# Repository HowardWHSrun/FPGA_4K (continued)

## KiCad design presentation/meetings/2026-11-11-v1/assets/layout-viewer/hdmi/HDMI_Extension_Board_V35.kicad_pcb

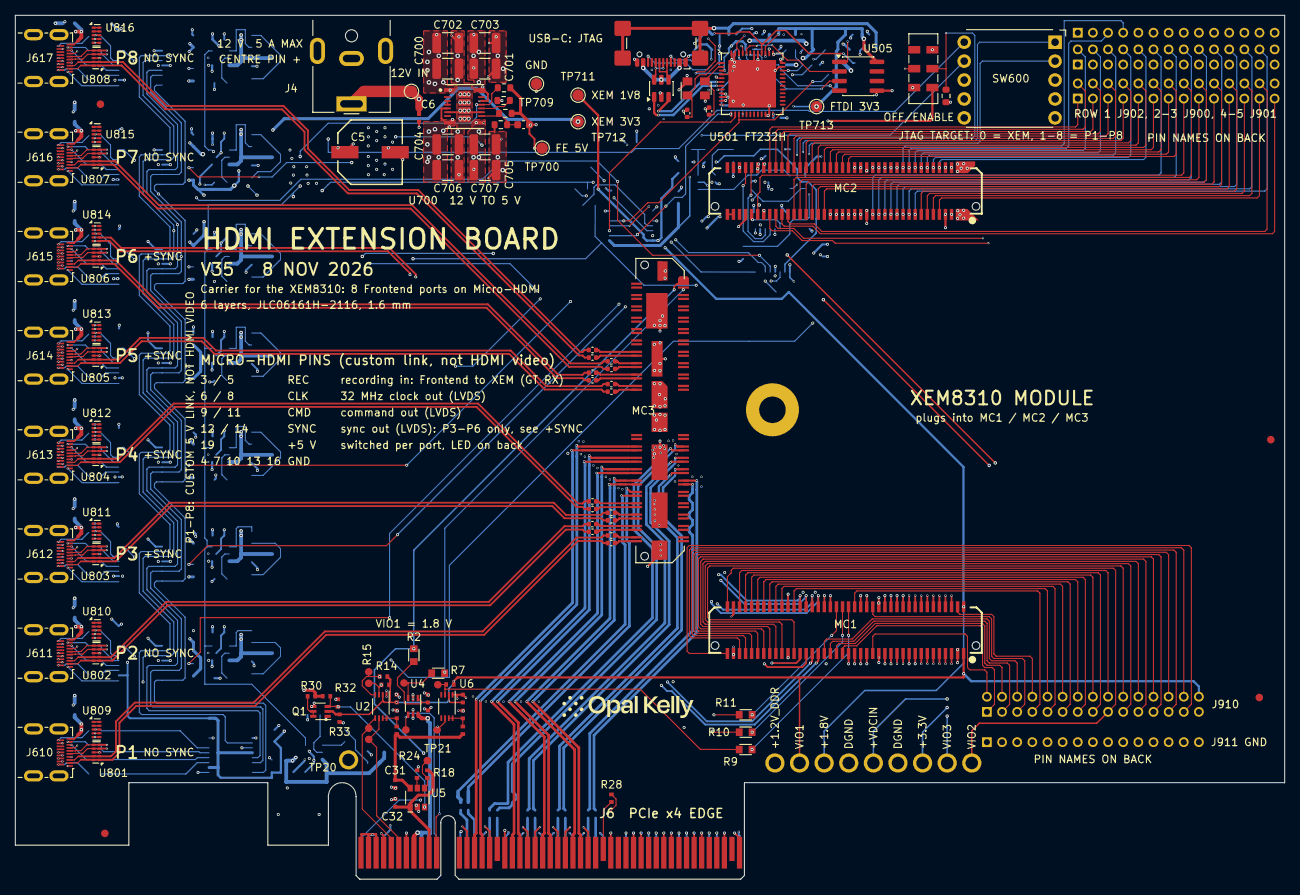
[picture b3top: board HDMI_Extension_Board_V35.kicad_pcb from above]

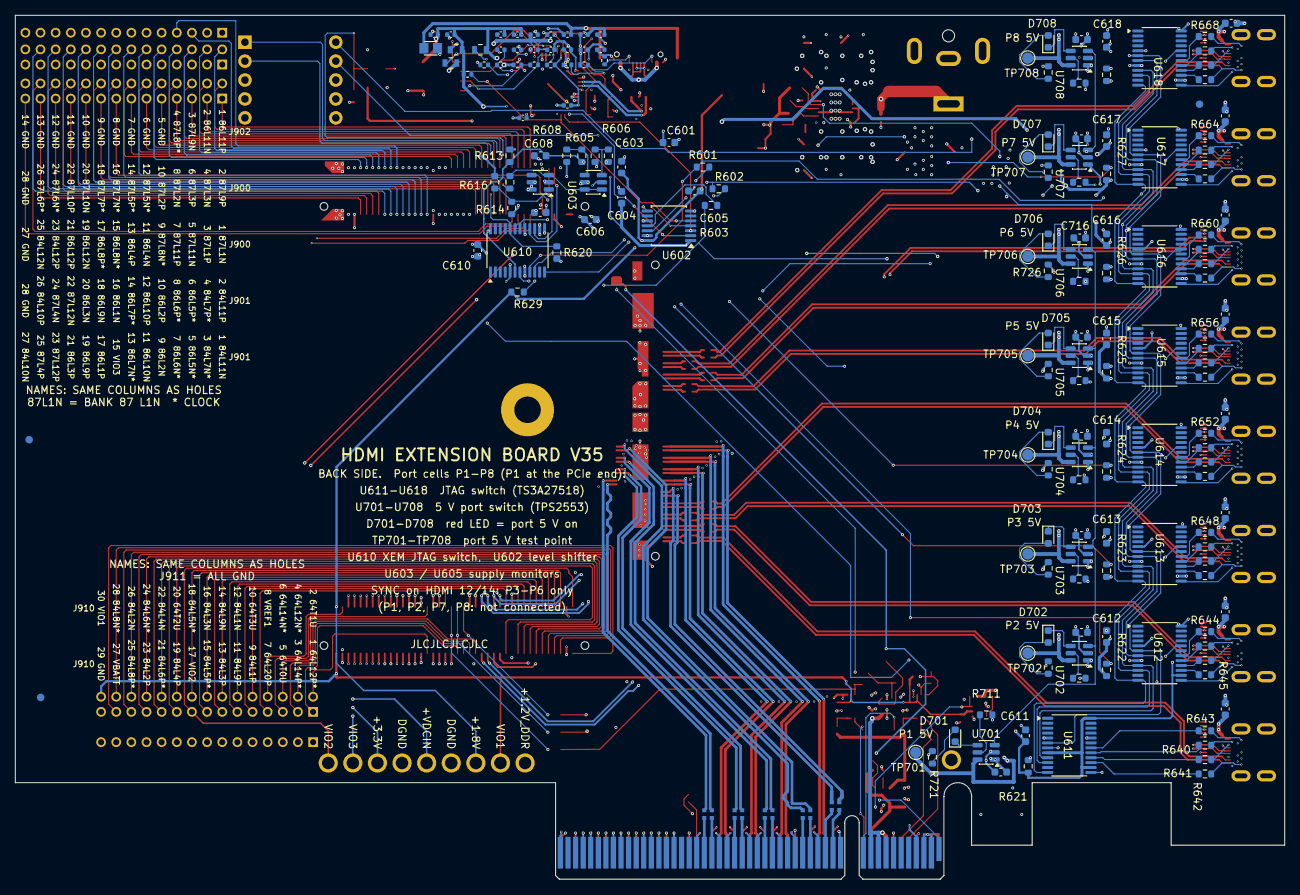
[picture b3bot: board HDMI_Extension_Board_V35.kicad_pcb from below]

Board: 6 copper layers, 167.6 x 114.1 mm, 309 parts (181 on the bottom side), 388 nets.

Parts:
*: Opal Kelly Logo; BRK_Logo_c689e08d
C5: EEE-FK1E221P; BRK_C5
C6: TMK105BJ104KV-F; BRK_C6
C7: C0402C104K8PACTU; BRK8310_C7
C8: C0402C104K8PACTU; BRK8310_C8
C9: C0402C104K8PACTU; BRK8310_C9
C10: C0402C104K8PACTU; BRK8310_C10
C11: C0402C104K8PACTU; BRK8310_C11
C12: C0402C104K8PACTU; BRK8310_C12
C13: CL05B224KO5NNNC; BRK8310_C13
C14: CL05B224KO5NNNC; BRK8310_C14
C15: CL05B224KO5NNNC; BRK8310_C15
C16: CL05B224KO5NNNC; BRK8310_C16
C17: CL05B224KO5NNNC; BRK8310_C17
C18: CL05B224KO5NNNC; BRK8310_C18
C19: CL05B224KO5NNNC; BRK8310_C19
C20: CL05B224KO5NNNC; BRK8310_C20
C27: C0402C104K8PACTU; BRK8310_C27
C28: C0402C104K8PACTU; BRK8310_C28
C31: C0402C104K8PACTU; BRK8310_C31
C32: C0402C104K8PACTU; BRK8310_C32
C500: 4.7u; C500
C501: 100n; C501
C502: 100n; C502
C503: 18p; C503
C504: 18p; C504
C505: 100n; C505
C506: 100n; C506
C507: 4.7u; C507
C508: 100n; C508
C509: 100n; C509
C510: 100n; C510
C511: 100n; C511
C512: 4.7u; C512
C513: 4.7u; C513
C514: 100n; C514
C515: 4.7u; C515
C516: 100n; C516
C517: 100n; C517
C518: 100n; C518
C519: 10n; C519
C601, C603: 2.2u; C_0603_1608Metric
C604, C605, C606, C609, C610, C611, C612, C613, C614, C615, C616, C617, C618: 100n; C_0603_1608Metric
C608: 1n; C_0603_1608Metric
C700, C701, C702, C703: 10uF; C_1210_3225Metric
C704, C705, C706, C707: 47uF; C_1210_3225Metric
C708: 22pF; C_0603_1608Metric
C711, C712, C713, C714, C715, C716, C717, C718: 100nF; C_0603_1608Metric
C721, C722, C723, C724, C725, C726, C727, C728: 1uF; C_0603_1608Metric
C745, C746, C747, C748, C749, C750, C751, C752, C753, C754, C755, C756, C757, C758, C759, C760: CL05B104KO5NNNC; C_0402_1005Metric
D500: USBLC6-2SC6; D500
D701, D702, D703, D704, D705, D706, D707, D708: RED; LED_0603_1608Metric
FB500: 600R; FB500
FB501: 600R; FB501
FB502: 600R; FB502
FB503: 220R @100MHz; FB503
FID1, FID5, FID6, FID7: FIDUCIAL; BRK_FID1
FID2: FIDUCIAL; BRK_FID2
FID3: FIDUCIAL; BRK_FID3
FID4: FIDUCIAL; BRK_FID4
J4: PJ-063AH; BarrelJack_CUI_PJ-063AH_Horizontal
J6: PCIe x8 Card-Edge Connector; BRK8310_J6
J500: USB4110-GF-A; J500
J610, J611, J612, J613, J614, J615, J616, J617: 467651001; HDMI_Micro-D_Molex_46765-1xxx
J900, J901: Conn_02x14_Odd_Even; HDR_Holes_2x14_P2.00mm
J902: Conn_01x14; HDR_Holes_1x14_P2.00mm
J910: Conn_02x15_Odd_Even; HDR_Holes_2x15_P2.00mm
J911: Conn_01x15; HDR_Holes_1x15_P2.00mm
J920: Voltage test holes; VHoles_1x09_P3.25mm_D1.651
MC1: BTE-040-01-F-D-A; BRK_MC1
MC2: BTE-040-01-F-D-A; BRK_MC2
MC3: QTH-040-01-F-D-DP-A; BRK_MC3
Q1: SI1922EDH-T1-GE3; BRK8310_Q1
R2: CRCW06030000Z0EA; BRK8310_R2
R7: CRCW06030000Z0EA; BRK8310_R7
R9: CRCW06030000Z0EA; BRK8310_R9
R10: CRCW06030000Z0EA; BRK8310_R10
R11: CRCW06030000Z0EA; BRK8310_R11
R13: CRCW0402200KFKED; BRK8310_R13
R14: CRCW04024K75FKED; BRK8310_R14
R15: CRCW04024K75FKED; BRK8310_R15
R18: CRCW0402100KFKED; BRK8310_R18
R23: CRCW0402200KFKED; BRK8310_R23
R24: CRCW0402100KFKED; BRK8310_R24
R25: CRCW0402100KFKED; BRK8310_R25
R28: CRCW04020000Z0ED; BRK8310_R28
R30: CRCW04024K75FKED; BRK8310_R30
R31: CRCW04024K75FKED; BRK8310_R31
R32: CRCW0402100KFKED; BRK8310_R32
R33: CRCW0402100KFKED; BRK8310_R33
R500: 5.1k 1%; R500
R501: 5.1k 1%; R501
R502: 100k; R502
R503: 100k; R503
R504: 2k; R504
R505: 10k; R505
R506: 10k; R506
R507: 12k 1%; R507
R509: 10k; R509
R600, R721, R722, R723, R724, R725, R726, R727, R728: 3.3k; R_0603_1608Metric
R601, R602, R603: 22R; R_0603_1608Metric
R605: 301k; R_0603_1608Metric
R606, R608, R616: 100k; R_0603_1608Metric
R607: 402k; R_0603_1608Metric
R613: 68k; R_0603_1608Metric
R614: 4.7k; R_0603_1608Metric
R615: 12k; R_0603_1608Metric
R620, R621, R622, R623, R624, R625, R626, R627, R628, R701, R703: 10k; R_0603_1608Metric
R629: 1k; R_0603_1608Metric
R640, R641, R642, R643, R644, R645, R646, R647, R648, R649, R650, R651, R652, R653, R654, R655, R656, R657, R658, R659, R660, R661, R662, R663, R664, R665, R666, R667, R668, R669, R670, R671: 100R; R_0603_1608Metric
R700: 40.2k; R_0603_1608Metric
R702: 13k; R_0603_1608Metric
R711, R712, R713, R714, R715, R716, R717, R718: 37.4k; R_0603_1608Metric
SW600: SRBQ490100; ALPS_SRBQ490100_1P9T
SW601: JS202011JCQN; SW700
TP9: SMDAT_VIO; BRK8310_TP9
TP10: SMDAT_PCIE; BRK8310_TP10
TP11: SMCLK_PCIE; BRK8310_TP11
TP12: SMCLK_VIO; BRK8310_TP12
TP13: PERST_VIO; BRK8310_TP13
TP14: PERST_PCIE; BRK8310_TP14
TP15: WAKE_VIO; BRK8310_TP15
TP16: WAKE_PCIE; BRK8310_TP16
TP20: +12V_PCIE_C; BRK8310_TP20
TP21: FAULT; BRK8310_TP21
TP700, TP701, TP702, TP703, TP704, TP705, TP706, TP707, TP708, TP709: TestPoint; TestPoint_Pad_D1.5mm
TP710: 12V_IN; TestPoint_Pad_D1.5mm
TP711: 1V8_XEM; TestPoint_Pad_D1.5mm
TP712: 3V3_XEM; TestPoint_Pad_D1.5mm
TP713: 3V3_FTDI; TestPoint_Pad_D1.5mm
U2: PCA9306DCUR; BRK8310_U2
U4: SN74AXC1T45DCK; BRK8310_U4
U5: AP22653AW6-7; BRK8310_U5
U6: PCA9306DCUR; BRK8310_U6
U501: FT232HQ-REEL; U501
U505: 93LC56BT-I/SN; SOIC-8_3.9x4.9mm_P1.27mm
U602: TXU0304PWR; TSSOP-14_4.4x5mm_P0.65mm
U603: TPS3700DDCR; SOT-23-6
U605: TPS3808G30DBVR; SOT-23-6
U610, U611, U612, U613, U614, U615, U616, U617, U618: TS3A27518EPWR; TSSOP-24_4.4x7.8mm_P0.65mm
U700: TPSM63606RDLR; TI_TPSM63606_RDL0020A_EVM
U701, U702, U703, U704, U705, U706, U707, U708: TPS2553DBVR; SOT-23-6
U801, U802, U803, U804, U805, U806, U807, U808, U809, U810, U811, U812, U813, U814, U815, U816: TPD4E02B04DQAR; USON-10_2.5x1.0mm_P0.5mm
Y500: 7U12000E18UCG 12MHz; Y500

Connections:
+1.2V_DDR: J920.1, MC3.80, R2.2
+1.8V: C603.1, C605.1, J920.3, MC1.2, R629.2, TP711.1, U602.14
+3.3V: C601.1, C606.1, C609.1, C610.1, C611.1, C612.1, C613.1, C614.1, C615.1, C616.1, C617.1, C618.1, J920.7, MC2.70, R30.2, R31.2, R615.1, R620.1, R621.1, R622.1, R623.1, R624.1, R625.1, R626.1, R627.1, R628.1, SW601.5, TP712.1, U603.5, U605.5, U605.6, U610.8, U610.14, U610.24, U611.8, U611.14, U611.24, U612.8, U612.14, U612.24, U613.8, U613.14, U613.24, U614.8, U614.14, U614.24, U615.8, U615.14, U615.24, U616.8, U616.14, U616.24, U617.8, U617.14, U617.24, U618.8, U618.14, U618.24
+3.3VAUX_PCIE: C31.2, R13.2, R23.2, U5.6
+3.3VAUX_PCIE_C: C32.2, J6.B10, R18.2, U5.1
+3.3V_PCIE_C: C12.2, J6.A9, J6.A10, J6.B8, U4.6
+VDCIN: C5.1, C6.2, C700.1, C701.1, C702.1, C703.1, J4.1, J920.5, MC2.1, MC2.2, MC2.3, MC2.4, TP710.1, U700.1, U700.14, U700.16
/+12V_PCIE_C: J6.A2, J6.A3, J6.B1, J6.B2, J6.B3, TP20.1
/FTDI3V3_PHY: C515.1, C516.1, FB501.2, U501.3
/FTDI3V3_PLL: C513.1, C514.1, FB500.2, U501.8
/FTDI5V_FILTERED: C500.1, C501.1, FB502.2, U501.40
/FTDI_EECLK: R503.2, U501.44, U505.2
/FTDI_EECS: R502.1, U501.45, U505.1
/FTDI_EEDATA: R504.1, U501.43, U505.3
/PCIE_PERST_B_3V3: J6.A11, TP14.1, U4.4
/PCIE_PERST_B_VIO: R7.1, TP13.1, U4.3
/PCIE_PRSNT1_B: J6.A1, R28.2
/PCIE_REFCLKN_C: C8.1, J6.A14
/PCIE_REFCLKP_C: C7.1, J6.A13
/PCIE_RX0N_C: C14.1, J6.A17
/PCIE_RX0P_C: C13.1, J6.A16
/PCIE_RX1N_C: C16.1, J6.A22
/PCIE_RX1P_C: C15.1, J6.A21
/PCIE_RX2N_C: C18.1, J6.A26
/PCIE_RX2P_C: C17.1, J6.A25
/PCIE_RX3N_C: C20.1, J6.A30
/PCIE_RX3P_C: C19.1, J6.A29
/PCIE_SMCLK_3V3: J6.B5, TP11.1, U2.5
/PCIE_SMCLK_VIO: R11.1, R14.1, TP12.1, U2.4
/PCIE_SMDAT_3V3: J6.B6, TP10.1, U2.6
/PCIE_SMDAT_VIO: R10.1, R15.1, TP9.1, U2.3
/PCIE_WAKE_B_3V3: J6.B11, TP16.1, U6.6
/PCIE_WAKE_B_VIO: R9.1, R25.1, TP15.1, U6.3
/VIO_PG: Q1.3, R31.1, R32.2, U5.3
B64_L1N: J614.8, MC1.12, U813.4, U813.7
B64_L1P: J614.6, MC1.10, U813.5, U813.6
B64_L2N: J615.11, MC1.16, U806.5, U806.6
B64_L2P: J615.9, MC1.14, U806.4, U806.7
B64_L3N: J611.11, MC1.15, U802.5, U802.6
B64_L3P: J611.9, MC1.13, U802.4, U802.7
B64_L4N: J614.11, MC1.8, U805.5, U805.6
B64_L4P: J614.9, MC1.6, U805.4, U805.7
B64_L5N: J610.11, MC1.7, U801.5, U801.6
B64_L5P: J610.9, MC1.5, U801.4, U801.7
B64_L6N: J610.8, MC1.11, U809.4, U809.7
B64_L6P: J610.6, MC1.9, U809.5, U809.6
B64_L7N: J612.11, MC1.23, U803.5, U803.6
B64_L7P: J612.9, MC1.21, U803.4, U803.7
B64_L8N: J615.8, MC1.20, U814.4, U814.7
B64_L8P: J615.6, MC1.18, U814.5, U814.6
B64_L9N: J616.11, MC1.24, U807.5, U807.6
B64_L9P: J616.9, MC1.22, U807.4, U807.7
B64_L10N: J616.8, MC1.28, U815.4, U815.7
B64_L10P: J616.6, MC1.26, U815.5, U815.6
B64_L11N_GC: J613.8, MC1.39, U812.4, U812.7
B64_L11P_GC: J613.6, MC1.37, U812.5, U812.6
B64_L12N_GC: J910.4, MC1.43
B64_L12P_GC: J910.1, MC1.41
B64_L13N_GC: J612.8, MC1.27, U811.4, U811.7
B64_L13P_GC: J612.6, MC1.25, U811.5, U811.6
B64_L14N_GC: J910.6, MC1.47
B64_L14P_GC: J910.3, MC1.45
B64_L15N: J613.11, MC1.35, U804.5, U804.6
B64_L15P: J613.9, MC1.33, U804.4, U804.7
B64_L16N: J612.14, MC1.51, U811.1, U811.10
B64_L16P: J612.12, MC1.49, U811.2, U811.9
B64_L17N: MC1.44, R11.2
B64_L17P: MC1.42, R10.2
B64_L18N: J615.14, MC1.56, U814.1, U814.10
B64_L18P: J615.12, MC1.54, U814.2, U814.9
B64_L19N: J611.8, MC1.19, U810.4, U810.7
B64_L19P: J611.6, MC1.17, U810.5, U810.6
B64_L20N: MC1.40, R9.2
B64_L20P: J910.7, MC1.38
B64_L21N: J617.11, MC1.36, U808.5, U808.6
B64_L21P: J617.9, MC1.34, U808.4, U808.7
B64_L22N: J614.14, MC1.52, U813.1, U813.10
B64_L22P: J614.12, MC1.50, U813.2, U813.9
B64_L23N: J613.14, MC1.55, U812.1, U812.10
B64_L23P: J613.12, MC1.53, U812.2, U812.9
B64_L24N: J617.8, MC1.48, U816.4, U816.7
B64_L24P: J617.6, MC1.46, U816.5, U816.6
B64_T0U_N12: J910.5, MC1.32
B64_T1U_N12: J910.2, MC1.31
B64_T2U_N12: J910.20, MC1.57
B64_T3U_N12: J910.10, MC1.58
B67_T3U_N12: MC3.78, R7.2
B84_L1N: J910.12, MC1.64
B84_L1P: J910.9, MC1.62
B84_L2N: J910.26, MC1.71
B84_L2P: J910.23, MC1.69
B84_L3N: J910.16, MC1.72
B84_L3P: J910.13, MC1.70
B84_L4N: J910.22, MC1.63
B84_L4P: J910.19, MC1.61
B84_L5N_HDGC: J910.18, MC1.76
B84_L5P_HDGC: J910.15, MC1.74
B84_L6N_HDGC: J910.24, MC1.67
B84_L6P_HDGC: J910.21, MC1.65
B84_L7N_HDGC: J901.3, MC2.62
B84_L7P_HDGC: J901.4, MC2.60
B84_L8N_HDGC: J910.28, MC1.75
B84_L8P_HDGC: J910.25, MC1.73
B84_L9N: J910.14, MC1.68
B84_L9P: J910.11, MC1.66
B84_L10N: J901.27, MC2.61
B84_L10P: J901.26, MC2.59
B84_L11N: J901.1, MC2.66
B84_L11P: J901.2, MC2.64
B84_L12N: J900.25, MC2.65
B84_L12P: J900.23, MC2.63
B86_L1N: J901.16, MC2.57
B86_L1P: J901.17, MC2.55
B86_L2N: J901.9, MC2.50
B86_L2P: J901.10, MC2.48
B86_L3N: J901.20, MC2.49
B86_L3P: J901.21, MC2.47
B86_L4N: J900.11, MC2.45
B86_L4P: J900.13, MC2.43
B86_L5N_HDGC: J901.5, MC2.58
B86_L5P_HDGC: J901.6, MC2.56
B86_L6N_HDGC: J901.7, MC2.54
B86_L6P_HDGC: J901.8, MC2.52
B86_L7N_HDGC: J901.13, MC2.42
B86_L7P_HDGC: J901.14, MC2.40
B86_L8N_HDGC: J900.15, MC2.41
B86_L8P_HDGC: J900.17, MC2.39
B86_L9N: J901.18, MC2.53
B86_L9P: J901.19, MC2.51
B86_L10N: J901.11, MC2.46
B86_L10P: J901.12, MC2.44
B86_L11N: J902.2, MC2.38
B86_L11P: J902.1, MC2.36
B86_L12N: J900.19, MC2.37
B86_L12P: J900.21, MC2.35
B87_L1N: J900.1, MC2.32
B87_L1P: J900.3, MC2.30
B87_L2N: J900.8, MC2.12
B87_L2P: J900.10, MC2.10
B87_L3N: J900.4, MC2.16
B87_L3P: J900.6, MC2.14
B87_L4N: J901.24, MC2.11
B87_L4P: J901.25, MC2.9
B87_L5N_HDGC: J900.12, MC2.31
B87_L5P_HDGC: J900.14, MC2.29
B87_L6N_HDGC: J900.24, MC2.19
B87_L6P_HDGC: J900.26, MC2.17
B87_L7N_HDGC: J900.16, MC2.27
B87_L7P_HDGC: J900.18, MC2.25
B87_L8N_HDGC: J900.9, MC2.24
B87_L8P_HDGC: J902.4, MC2.22
B87_L9N: J902.3, MC2.20
B87_L9P: J900.2, MC2.18
B87_L10N: J900.20, MC2.23
B87_L10P: J900.22, MC2.21
B87_L11N: J900.5, MC2.28
B87_L11P: J900.7, MC2.26
B87_L12N: J901.22, MC2.15
B87_L12P: J901.23, MC2.13
DGND: C5.2, C6.1, C9.1, C10.1, C11.1, C12.1, C27.1, C28.1, C31.1, C32.1, C500.2, C501.2, C502.2, C503.2, C504.2, C505.2, C506.1, C507.2, C508.2, C509.2, C510.2, C511.2, C512.2, C513.2, C514.2, C515.2, C516.2, C517.1, C518.1, C519.2, C601.2, C603.2, C604.2, C605.2, C606.2, C608.2, C609.2, C610.2, C611.2, C612.2, C613.2, C614.2, C615.2, C616.2, C617.2, C618.2, C700.2, C701.2, C702.2, C703.2, C704.2, C705.2, C706.2, C707.2, C711.2, C712.2, C713.2, C714.2, C715.2, C716.2, C717.2, C718.2, C721.2, C722.2, C723.2, C724.2, C725.2, C726.2, C727.2, C728.2, D500.2, FB503.1, J4.2, J6.A4, J6.A12, J6.A15, J6.A18, J6.A20, J6.A23, J6.A24, J6.A27, J6.A28, J6.A31, J6.A34, J6.A37, J6.A38, J6.A41, J6.A42, J6.A45, J6.A46, J6.A49, J6.B4, J6.B7, J6.B13, J6.B16, J6.B18, J6.B21, J6.B22, J6.B25, J6.B26, J6.B29, J6.B32, J6.B35, J6.B36, J6.B39, J6.B40, J6.B43, J6.B44, J6.B47, J6.B49, J500.A1, J500.A12, J500.B1, J500.B12, J610.4, J610.7, J610.10, J610.13, J610.16, J610.SH, J611.4, J611.7, J611.10, J611.13, J611.16, J611.SH, J612.4, J612.7, J612.10, J612.13, J612.16, J612.SH, J613.4, J613.7, J613.10, J613.13, J613.16, J613.SH, J614.4, J614.7, J614.10, J614.13, J614.16, J614.SH, J615.4, J615.7, J615.10, J615.13, J615.16, J615.SH, J616.4, J616.7, J616.10, J616.13, J616.16, J616.SH, J617.4, J617.7, J617.10, J617.13, J617.16, J617.SH, J900.27, J900.28, J901.28, J902.5, J902.6, J902.7, J902.8, J902.9, J902.10, J902.11, J902.12, J902.13, J902.14, J910.29, J911.1, J911.2, J911.3, J911.4, J911.5, J911.6, J911.7, J911.8, J911.9, J911.10, J911.11, J911.12, J911.13, J911.14, J911.15, J920.4, J920.6, MC1.3, MC1.29, MC1.30, MC1.59, MC1.60, MC1.77, MC1.78, MC2.5, MC2.6, MC2.7, MC2.8, MC2.33, MC2.34, MC2.67, MC2.68, MC2.73, MC3.0, Q1.1, Q1.4, R24.1, R32.1, R33.1, R500.1, R501.2, R502.2, R507.2, R600.2, R606.1, R608.1, R613.2, R616.2, R701.1, R702.1, R711.1, R712.1, R713.1, R714.1, R715.1, R716.1, R717.1, R718.1, SW601.1, SW601.7, TP709.1, U2.1, U4.2, U4.5, U5.2, U6.1, U501.4, U501.9, U501.10, U501.11, U501.22, U501.23, U501.35, U501.36, U501.41, U501.42, U501.47, U501.48, U501.PAD, U505.5, U602.7, U603.2, U605.2, U610.5, U611.5, U612.5, U613.5, U614.5, U615.5, U616.5, U617.5, U618.5, U700.6, U700.11, U700.17, U700.18, U700.19, U700.20, U701.2, U702.2, U703.2, U704.2, U705.2, U706.2, U707.2, U708.2, U801.3, U801.8, U802.3, U802.8, U803.3, U803.8, U804.3, U804.8, U805.3, U805.8, U806.3, U806.8, U807.3, U807.8, U808.3, U808.8, U809.3, U809.8, U810.3, U810.8, U811.3, U811.8, U812.3, U812.8, U813.3, U813.8, U814.3, U814.8, U815.3, U815.8, U816.3, U816.8, Y500.2, Y500.4
DRIVE_ENABLE: R615.2, R616.1, U602.8, U605.1
FE_5V: C704.1, C705.1, C706.1, C707.1, C708.1, C711.1, C712.1, C713.1, C714.1, C715.1, C716.1, C717.1, C718.1, R700.2, R703.2, R721.2, R722.2, R723.2, R724.2, R725.2, R726.2, R727.2, R728.2, TP700.1, U700.5, U700.8, U700.9, U701.1, U702.1, U703.1, U704.1, U705.1, U706.1, U707.1, U708.1
FTDI3V3: C505.1, C507.1, C508.1, C509.1, C510.1, C511.1, C512.1, C604.1, FB500.1, FB501.1, R503.1, R505.2, R506.1, R509.2, TP713.1, U501.12, U501.24, U501.39, U501.46, U505.8, U602.1
GNDADC: MC2.77, MC2.79
HDMI1_JTAG_TCK: J610.17, R640.2
HDMI1_JTAG_TDI: J610.15, R641.2
HDMI1_JTAG_TDO: J610.18, R643.2
HDMI1_JTAG_TMS: J610.2, R642.2
HDMI1_VREF: J610.1, U611.13
HDMI2_JTAG_TCK: J611.17, R644.2
HDMI2_JTAG_TDI: J611.15, R645.2
HDMI2_JTAG_TDO: J611.18, R647.2
HDMI2_JTAG_TMS: J611.2, R646.2
HDMI2_VREF: J611.1, U612.13
HDMI3_JTAG_TCK: J612.17, R648.2
HDMI3_JTAG_TDI: J612.15, R649.2
HDMI3_JTAG_TDO: J612.18, R651.2
HDMI3_JTAG_TMS: J612.2, R650.2
HDMI3_VREF: J612.1, U613.13
HDMI4_JTAG_TCK: J613.17, R652.2
HDMI4_JTAG_TDI: J613.15, R653.2
HDMI4_JTAG_TDO: J613.18, R655.2
HDMI4_JTAG_TMS: J613.2, R654.2
HDMI4_VREF: J613.1, U614.13
HDMI5_JTAG_TCK: J614.17, R656.2
HDMI5_JTAG_TDI: J614.15, R657.2
HDMI5_JTAG_TDO: J614.18, R659.2
HDMI5_JTAG_TMS: J614.2, R658.2
HDMI5_VREF: J614.1, U615.13
HDMI6_JTAG_TCK: J615.17, R660.2
HDMI6_JTAG_TDI: J615.15, R661.2
HDMI6_JTAG_TDO: J615.18, R663.2
HDMI6_JTAG_TMS: J615.2, R662.2
HDMI6_VREF: J615.1, U616.13
HDMI7_JTAG_TCK: J616.17, R664.2
HDMI7_JTAG_TDI: J616.15, R665.2
HDMI7_JTAG_TDO: J616.18, R667.2
HDMI7_JTAG_TMS: J616.2, R666.2
HDMI7_VREF: J616.1, U617.13
HDMI8_JTAG_TCK: J617.17, R668.2
HDMI8_JTAG_TDI: J617.15, R669.2
HDMI8_JTAG_TDO: J617.18, R671.2
HDMI8_JTAG_TMS: J617.2, R670.2
HDMI8_VREF: J617.1, U618.13
HOST_TCK: U501.13, U602.2
HOST_TDI: U501.14, U602.3
HOST_TDO: R509.1, U501.15, U602.5
HOST_TMS: U501.16, U602.4
JTAG_TCK: MC2.76, U610.17
JTAG_TCK_1V8: R601.2, U610.9, U611.9, U612.9, U613.9, U614.9, U615.9, U616.9, U617.9, U618.9
JTAG_TDI: MC2.74, U610.16
JTAG_TDI_1V8: R602.2, U610.12, U611.12, U612.12, U613.12, U614.12, U615.12, U616.12, U617.12, U618.12
JTAG_TDO: MC2.71, U610.18
JTAG_TDO_1V8: U602.10, U610.10, U611.10, U612.10, U613.10, U614.10, U615.10, U616.10, U617.10, U618.10
JTAG_TMS: MC2.72, U610.15
JTAG_TMS_1V8: R603.2, U610.7, U611.7, U612.7, U613.7, U614.7, U615.7, U616.7, U617.7, U618.7
MASTER: R600.1, R614.1, SW601.6
MGT_REFCLK1N_225_C: C8.2, MC3.19
MGT_REFCLK1P_225_C: C7.2, MC3.17
MGT_RXN0_224: C746.1, J610.5, U801.2, U801.9
MGT_RXN0_225: J6.B28, MC3.23
MGT_RXN0_226: C754.1, J614.5, U805.2, U805.9
MGT_RXN1_224: C748.1, J611.5, U802.2, U802.9
MGT_RXN1_225: J6.B24, MC3.27
MGT_RXN1_226: C756.1, J615.5, U806.2, U806.9
MGT_RXN2_224: C750.1, J612.5, U803.2, U803.9
MGT_RXN2_225: J6.B20, MC3.31
MGT_RXN2_226: C758.1, J616.5, U807.2, U807.9
MGT_RXN3_224: C752.1, J613.5, U804.2, U804.9
MGT_RXN3_225: J6.B15, MC3.35
MGT_RXN3_226: C760.1, J617.5, U808.2, U808.9
MGT_RXP0_224: C745.1, J610.3, U801.1, U801.10
MGT_RXP0_225: J6.B27, MC3.21
MGT_RXP0_226: C753.1, J614.3, U805.1, U805.10
MGT_RXP1_224: C747.1, J611.3, U802.1, U802.10
MGT_RXP1_225: J6.B23, MC3.25
MGT_RXP1_226: C755.1, J615.3, U806.1, U806.10
MGT_RXP2_224: C749.1, J612.3, U803.1, U803.10
MGT_RXP2_225: J6.B19, MC3.29
MGT_RXP2_226: C757.1, J616.3, U807.1, U807.10
MGT_RXP3_224: C751.1, J613.3, U804.1, U804.10
MGT_RXP3_225: J6.B14, MC3.33
MGT_RXP3_226: C759.1, J617.3, U808.1, U808.10
MGT_TXN0_225: C20.2, MC3.24
MGT_TXN1_225: C18.2, MC3.28
MGT_TXN2_225: C16.2, MC3.32
MGT_TXN3_225: C14.2, MC3.36
MGT_TXP0_225: C19.2, MC3.22
MGT_TXP1_225: C17.2, MC3.26
MGT_TXP2_225: C15.2, MC3.30
MGT_TXP3_225: C13.2, MC3.34
unnamed: C502.1, FB503.2, J500.M1, J500.M2, J500.M3, J500.M4
unnamed: D701.2, R721.1
unnamed: D701.1, U701.4
unnamed: D702.2, R722.1
unnamed: D702.1, U702.4
unnamed: D703.2, R723.1
unnamed: D703.1, U703.4
unnamed: D704.2, R724.1
unnamed: D704.1, U704.4
unnamed: D705.2, R725.1
unnamed: D705.1, U705.4
unnamed: D706.2, R726.1
unnamed: D706.1, U706.4
unnamed: D707.2, R727.1
unnamed: D707.1, U707.4
unnamed: D708.2, R728.1
unnamed: D708.1, U708.4
unnamed: J6.B31, R28.1
unnamed: J500.A5, R500.2
unnamed: J500.B5, R501.1
unnamed: C746.2, MC3.3
unnamed: C754.2, MC3.43
unnamed: C748.2, MC3.7
unnamed: C756.2, MC3.47
unnamed: C750.2, MC3.11
unnamed: C758.2, MC3.51
unnamed: C752.2, MC3.15
unnamed: C760.2, MC3.55
unnamed: C745.2, MC3.1
unnamed: C753.2, MC3.41
unnamed: C747.2, MC3.5
unnamed: C755.2, MC3.45
unnamed: C749.2, MC3.9
unnamed: C757.2, MC3.49
unnamed: C751.2, MC3.13
unnamed: C759.2, MC3.53
unnamed: Q1.5, Q1.6, R30.1
unnamed: R18.1, TP21.1, U5.4
unnamed: C10.2, R13.1, U2.7, U2.8
unnamed: C11.2, R2.1, U4.1
unnamed: R24.2, U5.5
unnamed: C28.2, R23.1, U6.7, U6.8
unnamed: C503.1, U501.1, Y500.1
unnamed: C504.1, U501.2, Y500.3
unnamed: R507.1, U501.5
unnamed: C518.2, U501.37
unnamed: C517.2, U501.38
unnamed: C519.1, R506.2, U501.34
unnamed: R504.2, R505.1, U505.4
unnamed: R601.1, U602.13
unnamed: R602.1, U602.12
unnamed: R603.1, U602.11
unnamed: R605.2, R606.2, U603.3
unnamed: R607.2, R608.2, U603.4
unnamed: R629.1, U610.13
unnamed: R642.1, U611.15
unnamed: R640.1, U611.17
unnamed: R643.1, U611.18
unnamed: R641.1, U611.16
unnamed: R646.1, U612.15
unnamed: R644.1, U612.17
unnamed: R647.1, U612.18
unnamed: R645.1, U612.16
unnamed: R650.1, U613.15
unnamed: R648.1, U613.17
unnamed: R651.1, U613.18
unnamed: R649.1, U613.16
unnamed: R654.1, U614.15
unnamed: R652.1, U614.17
unnamed: R655.1, U614.18
unnamed: R653.1, U614.16
unnamed: R658.1, U615.15
unnamed: R656.1, U615.17
unnamed: R659.1, U615.18
unnamed: R657.1, U615.16
unnamed: R662.1, U616.15
unnamed: R660.1, U616.17
unnamed: R663.1, U616.18
unnamed: R661.1, U616.16
unnamed: R666.1, U617.15
unnamed: R664.1, U617.17
unnamed: R667.1, U617.18
unnamed: R665.1, U617.16
unnamed: R670.1, U618.15
unnamed: R668.1, U618.17
unnamed: R671.1, U618.18
unnamed: R669.1, U618.16
unnamed: U700.3, U700.4
unnamed: C708.2, R700.1, R701.2, U700.10
unnamed: R702.2, U700.12
unnamed: R711.2, U701.5
unnamed: R712.2, U702.5
unnamed: R713.2, U703.5
unnamed: R714.2, U704.5
unnamed: R715.2, U705.5
unnamed: R716.2, U706.5
unnamed: R717.2, U707.5
unnamed: R718.2, U708.5
unnamed: U809.1, U809.10
unnamed: U809.2, U809.9
unnamed: U810.1, U810.10
unnamed: U810.2, U810.9
unnamed: U815.1, U815.10
unnamed: U815.2, U815.9
unnamed: U816.1, U816.10
unnamed: U816.2, U816.9
PORT1_5V: C721.1, J610.19, TP701.1, U701.6
PORT2_5V: C722.1, J611.19, TP702.1, U702.6
PORT3_5V: C723.1, J612.19, TP703.1, U703.6
PORT4_5V: C724.1, J613.19, TP704.1, U704.6
PORT5_5V: C725.1, J614.19, TP705.1, U705.6
PORT6_5V: C726.1, J615.19, TP706.1, U706.6
PORT7_5V: C727.1, J616.19, TP707.1, U707.6
PORT8_5V: C728.1, J617.19, TP708.1, U708.6
PORT_ENABLE: R703.1, U700.13, U701.3, U702.3, U703.3, U704.3, U705.3, U706.3, U707.3, U708.3
ROTARY_COMMON: SW600.3, SW601.2
SEL_0: R620.2, SW600.1, U610.20
SEL_1: R621.2, SW600.2, U611.20
SEL_2: R622.2, SW600.4, U612.20
SEL_3: R623.2, SW600.5, U613.20
SEL_4: R624.2, SW600.6, U614.20
SEL_5: R625.2, SW600.7, U615.20
SEL_6: R626.2, SW600.8, U616.20
SEL_7: R627.2, SW600.9, U617.20
SEL_8: R628.2, SW600.10, U618.20
USB5V: C506.2, D500.5, FB502.1, J500.A4, J500.A9, J500.B4, J500.B9
USB_DM_CONN: D500.4, J500.A7, J500.B7
USB_DP_CONN: D500.6, J500.A6, J500.B6
USB_D_N: D500.3, U501.6
USB_D_P: D500.1, U501.7
VBATT: J910.27, MC1.79
VIO1: C9.2, C27.2, J910.30, J920.2, MC1.1, Q1.2, R14.2, R15.2, R25.2, R33.2, U2.2, U6.2
VIO2: J910.17, J920.9, MC1.80
VIO3: J901.15, J920.8, MC2.69
VREF1: J910.8, MC1.4
VREF_SELECTED: C608.1, R605.1, R607.1, R613.1, U610.6, U611.6, U612.6, U613.6, U614.6, U615.6, U616.6, U617.6, U618.6
WINDOW_GATE: R614.2, U603.1, U603.6, U605.3

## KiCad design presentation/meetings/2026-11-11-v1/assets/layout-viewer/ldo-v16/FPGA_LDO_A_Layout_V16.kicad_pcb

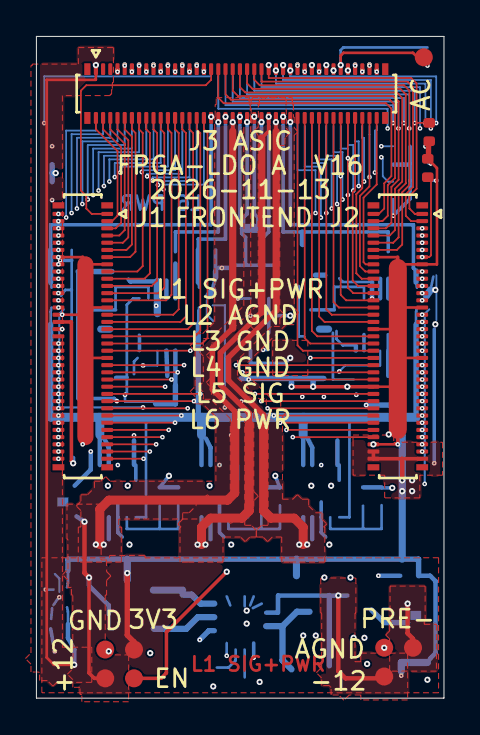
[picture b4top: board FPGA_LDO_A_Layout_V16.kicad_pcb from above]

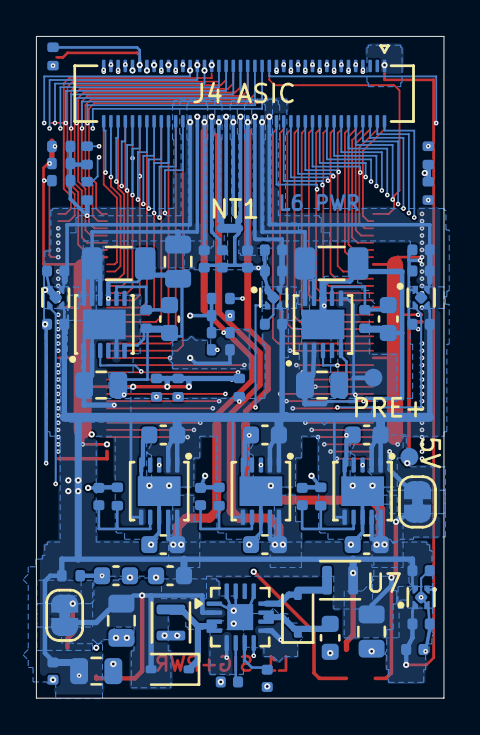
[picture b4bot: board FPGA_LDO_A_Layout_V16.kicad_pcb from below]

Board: 6 copper layers, 22.6 x 36.8 mm, 93 parts (80 on the bottom side), 149 nets.

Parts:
C1, C14, C21: 22uF; C_0805_2012Metric
C2: 100nF; C_0402_1005Metric
C3, C11: 4.7uF; C_0603_1608Metric
C15, C903, C1003: 1uF; C_0603_1608Metric
C16, C17: 10nF; C_0402_1005Metric
C51, C53, C54, C55, C56, C57, C203, C301, C302, C401, C402, C501, C502, C603, C701, C702, C803: 1uF; C_0402_1005Metric
C201, C202, C601, C602, C801, C802: 10uF; C_0603_1608Metric
C901, C1001, C1004: 10uF; C_0805_2012Metric
C902, C1002: 22uF; C_1206_3216Metric
D11, D12: B0540WS-TP; D_SOD-323
J1, J2: DF40C-70DP-0.4V(51); Hirose_DF40C-70DP-0.4V_2x35-1MP_P0.4mm
J3: DF40C-80DP-0.4V(51); Hirose_DF40C-80DP-0.4V_2x40-1MP_P0.4mm
J4: DF40C-80DS-0.4V(51); Hirose_DF40C-80DS-0.4V_2x40_P0.4mm
JP1, JP2: Bridged; SolderJumper-2_P1.3mm_Bridged_RoundedPad1.0x1.5mm
L11, L12: 6.8uH; L_Murata_DFE201610P
NT1: NetTie_2; NetTie-2_SMD_Pad0.5mm
R1, R2, R3, R4, R5, R6, R16, R17, R18, R19, R20, R21, R22, R23, R24, R25, R26, R27: 10k; R_0402_1005Metric
R201, R601: 15k; R_0402_1005Metric
R801: 7.5k; R_0402_1005Metric
R901, R1001: 80.6k; R_0402_1005Metric
TP1: VIN_3V3; TestPoint_Pad_D1.0mm_Compact
TP2: STIM_POS_12V; TestPoint_Pad_D1.0mm_Compact
TP3: STIM_NEG_12V; TestPoint_Pad_D1.0mm_Compact
TP4: EN_ASIC_RAILS; TestPoint_Pad_D1.0mm_Compact
TP5: GND; TestPoint_Pad_D1.0mm_Compact
TP6: AGND; TestPoint_Pad_D1.0mm_Compact
TP7: ASIC_AC_IN; TestPoint_Pad_D1.0mm_Compact
TP8: STIM_PRE_POS; TestPoint_Pad_D1.0mm_Compact
TP9: STIM_PRE_NEG; TestPoint_Pad_D1.0mm_Compact
TP10: VIN_5V; TestPoint_Pad_D1.0mm_Compact
U1: LT3582EUD-12#PBF; QFN-16-1EP_3x3mm_P0.5mm_EP1.45x1.45mm
U2, U6, U8, U9: LT3042EDD#PBF; DFN-10-1EP_3x3mm_P0.5mm_EP1.65x2.38mm
U3, U4, U5, U7: TPS7A2015PDQNR; Texas_X2SON-4_1x1mm_P0.65mm
U10: LT3094EDD#PBF; DFN-12-1EP_3x3mm_P0.45mm_EP1.65x2.38mm

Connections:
/ASIC1_CLK32MHz_Out: J2.59, J4.45
/ASIC1_DATA1: J2.21, J4.79
/ASIC1_DATA2: J2.64, J4.77
/ASIC1_DATA3: J2.62, J4.75
/ASIC1_DATA4: J2.60, J4.73
/ASIC1_DATA5: J2.57, J4.43
/ASIC1_DATA6: J2.55, J4.41
/ASIC1_DATA7: J2.53, J4.39
/ASIC1_DATA8: J2.51, J4.37
/ASIC1_READ: J2.49, J4.35
/ASIC1_SYNC: J2.61, J4.47
/ASIC2_CLK32MHz_Out: J1.63, J4.19
/ASIC2_DATA1: J1.70, J4.33
/ASIC2_DATA2: J1.51, J4.31
/ASIC2_DATA3: J1.53, J4.29
/ASIC2_DATA4: J1.55, J4.27
/ASIC2_DATA5: J1.65, J4.17
/ASIC2_DATA6: J1.67, J4.15
/ASIC2_DATA7: J1.69, J4.13
/ASIC2_DATA8: J1.38, J4.11
/ASIC2_READ: J1.40, J4.9
/ASIC2_SYNC: J1.61, J4.21
/ASIC3_4_TOP_SPI_CLK: J2.37, J4.72, R24.1
/ASIC3_4_TOP_SPI_LATCH: J2.35, J4.70, R26.1
/ASIC3_CLK32MHz_Out: J2.25, J4.62
/ASIC3_DATA1: J2.47, J4.80
/ASIC3_DATA2: J2.45, J4.78
/ASIC3_DATA3: J2.43, J4.76
/ASIC3_DATA4: J2.39, J4.74
/ASIC3_DATA5: J2.23, J4.60
/ASIC3_DATA6: J2.42, J4.58
/ASIC3_DATA7: J1.39, J4.32
/ASIC3_DATA8: J1.43, J4.30
/ASIC3_READ: J1.45, J4.28
/ASIC3_SPI_DL: J2.33, J4.68
/ASIC3_SPI_DR: J2.31, J4.66
/ASIC3_SYNC: J2.29, J4.64
/ASIC4_CLK32MHz_Out: J1.56, J4.12
/ASIC4_DATA1: J1.47, J4.26
/ASIC4_DATA2: J1.49, J4.24
/ASIC4_DATA3: J1.44, J4.22
/ASIC4_DATA4: J1.46, J4.20
/ASIC4_DATA5: J1.58, J4.10
/ASIC4_DATA6: J1.60, J4.8
/ASIC4_DATA7: J1.62, J4.6
/ASIC4_DATA8: J1.64, J4.4
/ASIC4_READ: J1.68, J4.2
/ASIC4_SPI_DL: J1.48, J4.18
/ASIC4_SPI_DR: J1.52, J4.16
/ASIC4_SYNC: J1.54, J4.14
/ASIC5_CLK32MHz_Out: J2.12, J3.45
/ASIC5_DATA1: J2.5, J3.79
/ASIC5_DATA2: J2.7, J3.77
/ASIC5_DATA3: J2.9, J3.75
/ASIC5_DATA4: J2.11, J3.73
/ASIC5_DATA5: J2.10, J3.43
/ASIC5_DATA6: J2.8, J3.41
/ASIC5_DATA7: J2.6, J3.39
/ASIC5_DATA8: J2.4, J3.37
/ASIC5_READ: J2.2, J3.35
/ASIC5_SYNC: J2.3, J3.47
/ASIC6_CLK32MHz_Out: J1.16, J3.19
/ASIC6_DATA1: J1.1, J3.33
/ASIC6_DATA2: J1.28, J3.31
/ASIC6_DATA3: J1.26, J3.29
/ASIC6_DATA4: J1.24, J3.27
/ASIC6_DATA5: J1.12, J3.17
/ASIC6_DATA6: J1.10, J3.15
/ASIC6_DATA7: J1.8, J3.13
/ASIC6_DATA8: J1.6, J3.11
/ASIC6_READ: J1.4, J3.9
/ASIC6_SYNC: J1.18, J3.21
/ASIC7_8_TOP_SPI_CLK: J2.24, J3.72, R25.1
/ASIC7_8_TOP_SPI_LATCH: J2.26, J3.70, R27.1
/ASIC7_CLK32MHz_Out: J2.36, J3.62
/ASIC7_DATA1: J2.16, J3.80
/ASIC7_DATA2: J2.18, J3.78
/ASIC7_DATA3: J2.20, J3.76
/ASIC7_DATA4: J2.22, J3.74
/ASIC7_DATA5: J2.38, J3.60
/ASIC7_DATA6: J2.40, J3.58
/ASIC7_DATA7: J1.37, J3.32
/ASIC7_DATA8: J1.35, J3.30
/ASIC7_READ: J1.33, J3.28
/ASIC7_SPI_DL: J2.28, J3.68
/ASIC7_SPI_DR: J2.30, J3.66
/ASIC7_SYNC: J2.32, J3.64
/ASIC8_CLK32MHz_Out: J1.13, J3.12
/ASIC8_DATA1: J1.31, J3.26
/ASIC8_DATA2: J1.29, J3.24
/ASIC8_DATA3: J1.25, J3.22
/ASIC8_DATA4: J1.23, J3.20
/ASIC8_DATA5: J1.11, J3.10
/ASIC8_DATA6: J1.9, J3.8
/ASIC8_DATA7: J1.7, J3.6
/ASIC8_DATA8: J1.5, J3.4
/ASIC8_READ: J1.3, J3.2
/ASIC8_SPI_DL: J1.21, J3.18
/ASIC8_SPI_DR: J1.19, J3.16
/ASIC8_SYNC: J1.17, J3.14
/ASIC_AC_IN: J3.69, J4.69, R6.1, TP7.1
/ASIC_DVDD: C54.1, C502.1, J3.34, J4.34, R19.2, U5.1
/ASIC_REF_VCM: C57.1, C802.1, J3.40, J4.40, U8.9, U8.10
/ASIC_REF_VDD: C55.1, C602.1, J3.52, J4.52, U6.9, U6.10
/ASIC_VDD10: C902.1, J3.36, J4.36, U9.9, U9.10
/ASIC_VDD_ADC: C302.1, J3.56, J4.56, U3.1
/ASIC_VDD_CGEN: C56.1, C702.1, J3.1, J4.1, U7.1
/ASIC_VDD_DRIVER: C53.1, C402.1, J3.38, J4.38, U4.1
/ASIC_VDD_FE: C51.1, C202.1, J3.50, J4.50, U2.9, U2.10
/ASIC_VSS10: C1002.1, C1004.1, J3.54, J4.54, U10.10, U10.11, U10.12
/BOARD1_CLK: J1.42, J4.7, R20.1
/BOARD1_SPI_CLK: J2.52, J4.63, R22.1
/BOARD3_CLK: J1.2, J3.7, R21.1
/BOARD3_SPI_CLK: J2.13, J3.63, R23.1
/CAPP: C15.1, D11.1, U1.10, U1.11
/CHIP_RESET_SHARED: J2.58, J3.71, J4.71, R19.1
/EN_ASIC_RAILS: C3.1, R1.2, TP4.1, U1.8, U2.3, U3.3, U4.3, U5.3, U6.3, U7.3, U8.3, U9.3, U10.3
/FE_RESET_SHARED: J2.54, J3.65, J4.65, R16.1
/IMP_TST_SHARED: J2.56, J3.67, J4.67, R17.1
/RAMPN: C17.1, U1.6
/RAMPP: C16.1, U1.7
/SPI_LATCH_SHARED: J2.48, J3.61, J4.61, R18.1
/STIM_CHB_SHARED: J2.1, J3.49, J4.49, R4.1
/STIM_CHIP1_SPI_DL: J2.46, J4.59
/STIM_CHIP1_SPI_DR: J2.44, J4.57
/STIM_CHIP2_SPI_DL: J1.57, J4.25
/STIM_CHIP2_SPI_DR: J1.59, J4.23
/STIM_CHIP3_SPI_DL: J2.17, J3.59
/STIM_CHIP3_SPI_DR: J2.19, J3.57
/STIM_CHIP4_SPI_DL: J1.22, J3.25
/STIM_CHIP4_SPI_DR: J1.20, J3.23
/STIM_CLK_SHARED: J2.65, J3.53, J4.53, R5.1
/STIM_EN_SHARED: J2.63, J3.51, J4.51, R2.1
/STIM_NEG_12V: C21.1, D12.2, JP2.1, TP3.1, U1.2
/STIM_POS_12V: C14.1, JP1.1, TP2.1, U1.9
/STIM_PRE_NEG: C1001.1, JP2.2, TP9.1, U10.1, U10.2, U10.5, U10.13
/STIM_PRE_POS: C901.1, JP1.2, TP8.1, U9.1, U9.2, U9.6
/STIM_START_SHARED: J2.67, J3.55, J4.55, R3.1
/SW_N: D12.1, L12.1, U1.3, U1.4
/SW_P: D11.2, L11.2, U1.12
/VIN_3V3: C1.1, C2.1, C11.1, C201.1, C301.1, C401.1, C501.1, C601.1, C701.1, C801.1, J2.68, J2.69, J2.70, L11.1, R1.1, TP1.1, U1.5, U2.1, U2.2, U2.6, U3.4, U4.4, U5.4, U6.1, U6.2, U6.6, U7.4, U8.1, U8.2, U8.6
/VIN_5V: J1.32, TP10.1
AGND: C51.2, C53.2, C55.2, C56.2, C57.2, C201.2, C202.2, C203.2, C301.2, C302.2, C401.2, C402.2, C601.2, C602.2, C603.2, C701.2, C702.2, C801.2, C802.2, C803.2, C901.2, C902.2, C903.2, C1001.2, C1002.2, C1003.2, C1004.2, J3.42, J3.44, J4.42, J4.44, NT1.2, R6.2, R201.2, R601.2, R801.2, R901.2, R1001.2, TP6.1, U2.5, U2.8, U2.11, U3.2, U3.5, U4.2, U4.5, U6.5, U6.8, U6.11, U7.2, U7.5, U8.5, U8.8, U8.11, U9.5, U9.8, U9.11, U10.6, U10.9
GND: C1.2, C2.2, C3.2, C11.2, C14.2, C15.2, C16.2, C17.2, C21.2, C54.2, C501.2, C502.2, J1.14, J1.15, J1.27, J1.30, J1.34, J1.41, J1.50, J1.66, J2.14, J2.15, J2.27, J2.34, J2.41, J2.50, J2.66, J3.46, J3.48, J4.46, J4.48, L12.2, NT1.1, R2.2, R3.2, R4.2, R5.2, R16.2, R17.2, R18.2, R20.2, R21.2, R22.2, R23.2, R24.2, R25.2, R26.2, R27.2, TP5.1, U1.1, U1.13, U1.15, U1.16, U1.17, U5.2, U5.5
unnamed: C203.1, R201.1, U2.7
unnamed: C603.1, R601.1, U6.7
unnamed: C803.1, R801.1, U8.7
unnamed: C903.1, R901.1, U9.7
unnamed: C1003.1, R1001.1, U10.8
